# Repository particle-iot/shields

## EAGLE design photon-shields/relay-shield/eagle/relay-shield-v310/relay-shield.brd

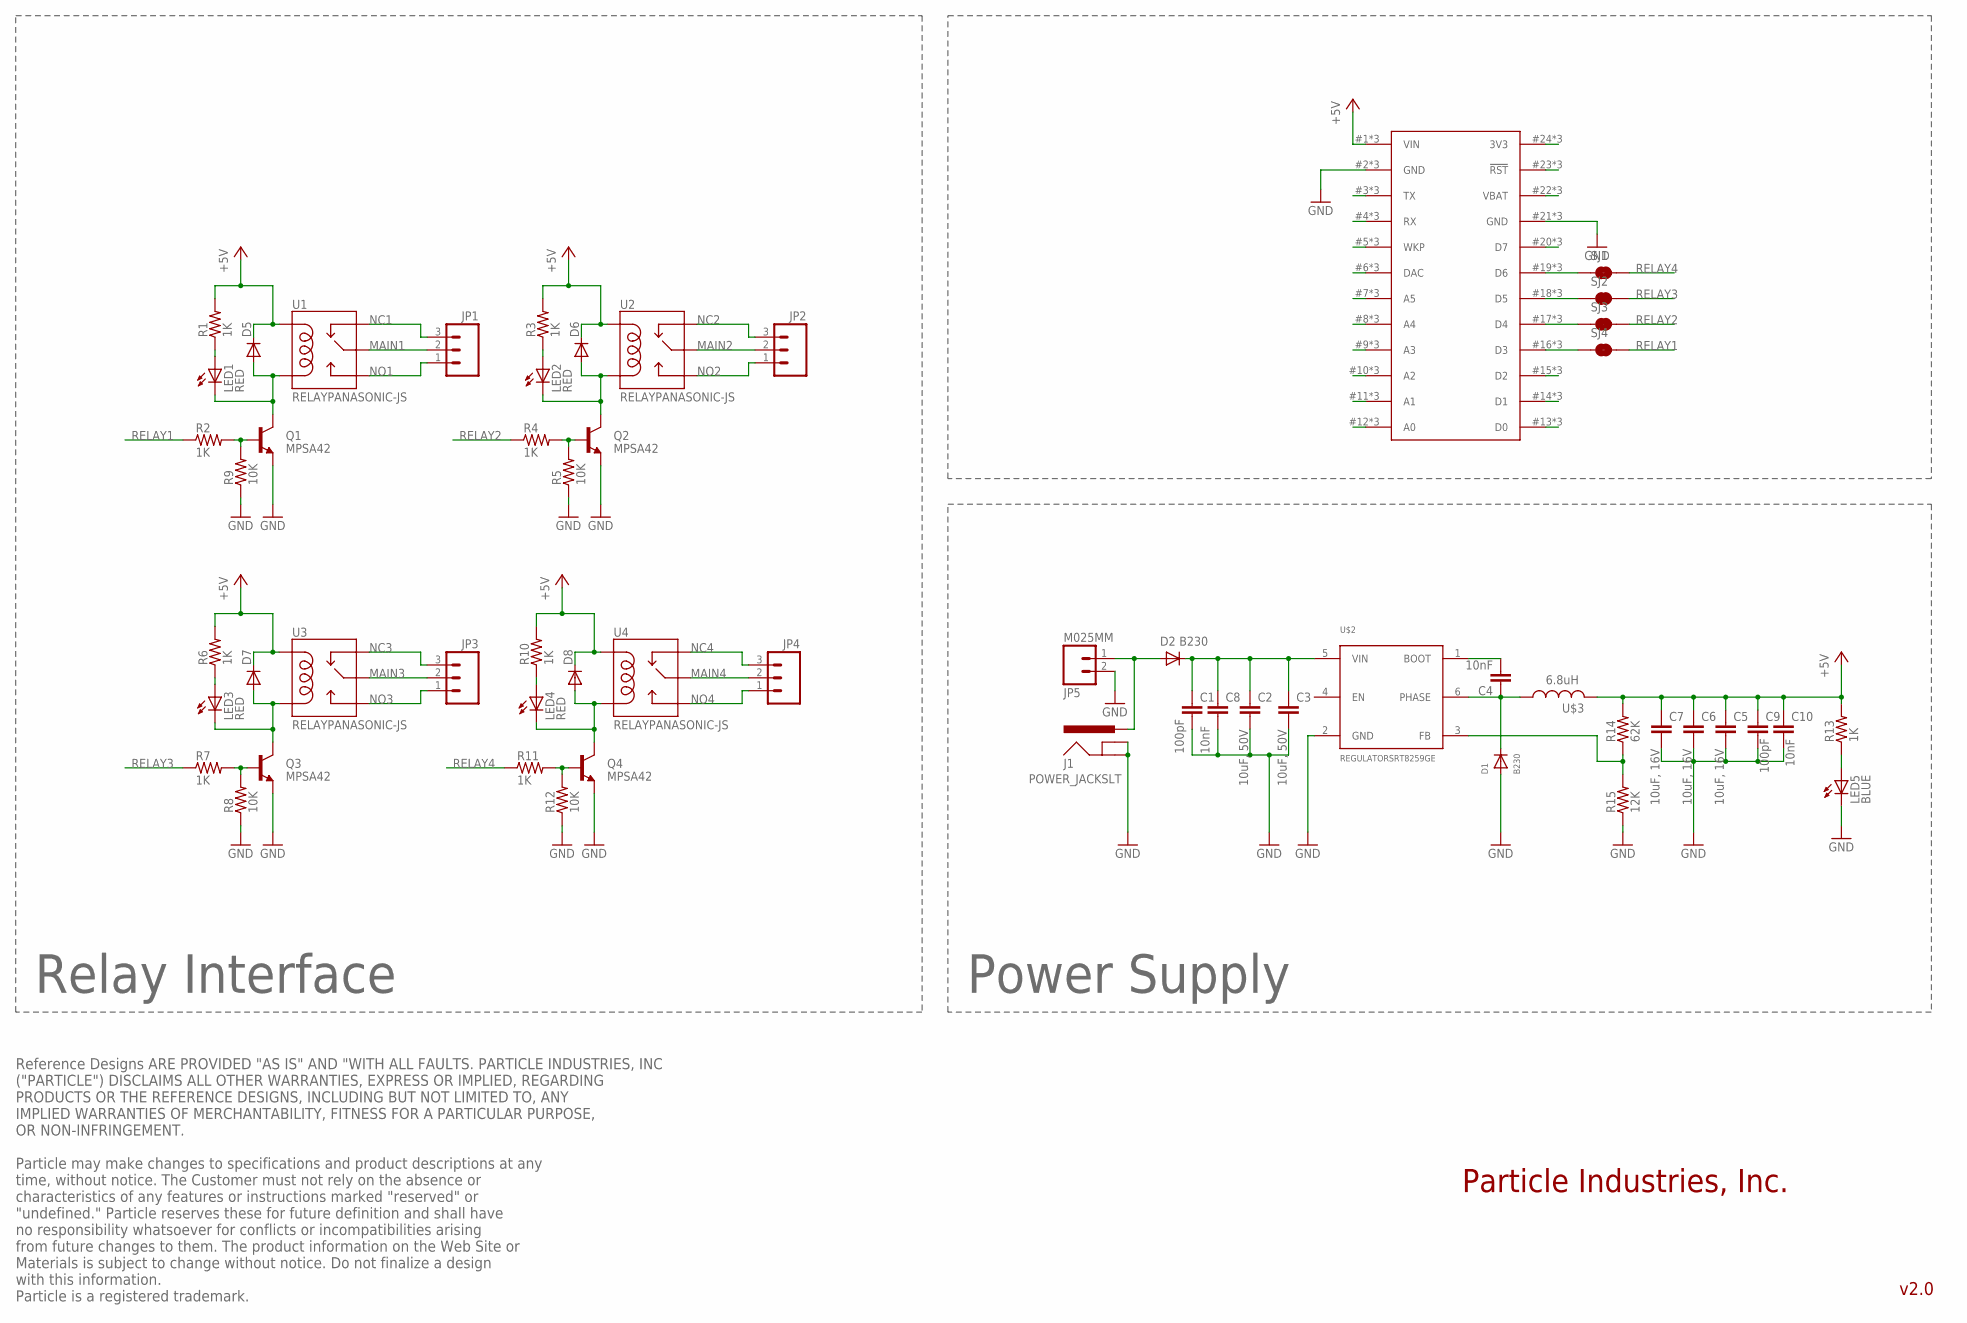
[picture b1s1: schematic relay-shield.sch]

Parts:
C1, C9: 100pF; C0603
C2, C3: 10uF, 50V; 1206
C4: 10nF; 0603-CAP
C5, C6, C7: 10uF, 16V; 1206
C8, C10: 10nF; C0603
D1, D2: B230; SMADIODE
D5, D6, D7, D8: DIODE-SOD123; SOD123
J1: POWER_JACKSLT; POWER_JACK_SLOT
JP1, JP2, JP3, JP4: M03-SCREW-5MM; SCREWTERMINAL-5MM-3
JP5: M025MM; SCREWTERMINAL-5MM-2
LED1, LED2, LED3, LED4: RED; LED-0603
LED5: BLUE; LED-0603
Q1, Q2, Q3, Q4: MPSA42; SOT23
R1, R2, R3, R4, R6, R7, R10, R11, R13: 1K; 0603-RES
R5, R8, R9, R12: 10K; 0603-RES
R14: 62K; 0603-RES
R15: 12K; 0603-RES
SJ1, SJ2, SJ3, SJ4: JUMPER-PAD-2-NC_BY_TRACE; PAD-JUMPER-2-NC_BY_TRACE_YES_SILK
U1, U2, U3, U4: RELAYPANASONIC-JS; JS1-5V-F
U$1: SPARK_CORESTACKABLE; SPARK_CORE_STACKABLE
U$2: REGULATORSRT8259GE; SOT23-6
U$3: INDUCTORS; NR8040T6R8N

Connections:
+5V: C5.1, C6.1, C7.1, C9.1, C10.1, D5.C, D6.C, D7.C, D8.C, R1.2, R3.2, R6.2, R10.2, R13.2, R14.2, U1.COIL1, U2.COIL1, U3.COIL1, U4.COIL1, U$1.1 (VIN), U$1.#1 (VIN), U$1.@1 (VIN), U$3.P$2 (2)
GND: C1.2, C2.2, C3.2, C5.2, C6.2, C7.2, C8.2, C9.2, C10.2, D1.A, J1.GND@1 (GNDBREAK), J1.GND@2 (GND), JP5.2, LED5.C, Q1.2 (E), Q2.2 (E), Q3.2 (E), Q4.2 (E), R5.1, R8.1, R9.1, R12.1, R15.1, U$1.2 (GND), U$1.21 (GND), U$1.#2 (GND), U$1.#21 (GND), U$1.@2 (GND), U$1.@21 (GND), U$2.2 (GND)
MAIN1: JP1.2, U1.COMMON (MAIN)
MAIN2: JP2.2, U2.COMMON (MAIN)
MAIN3: JP3.2, U3.COMMON (MAIN)
MAIN4: JP4.2, U4.COMMON (MAIN)
unnamed: D5.A, LED1.C, Q1.3 (C), U1.COIL2
unnamed: Q2.1 (B), R4.2, R5.2
unnamed: Q1.1 (B), R2.2, R9.2
unnamed: LED1.A, R1.1
unnamed: D6.A, LED2.C, Q2.3 (C), U2.COIL2
unnamed: LED2.A, R3.1
unnamed: Q3.1 (B), R7.2, R8.2
unnamed: D7.A, LED3.C, Q3.3 (C), U3.COIL2
unnamed: LED3.A, R6.1
unnamed: Q4.1 (B), R11.2, R12.2
unnamed: D8.A, LED4.C, Q4.3 (C), U4.COIL2
unnamed: LED4.A, R10.1
unnamed: U$1.15 (D2), U$1.#15 (D2), U$1.@15 (D2)
unnamed: C1.1, C2.1, C3.1, C8.1, D2.C, U$2.5 (VIN)
unnamed: U$1.14 (D1), U$1.#14 (D1), U$1.@14 (D1)
unnamed: LED5.A, R13.1
unnamed: U$1.13 (D0), U$1.#13 (D0), U$1.@13 (D0)
unnamed: U$1.20 (D7), U$1.#20 (D7), U$1.@20 (D7)
unnamed: U$1.22 (VBAT), U$1.#22 (VBAT), U$1.@22 (VBAT)
unnamed: U$1.23 (!RST), U$1.#23 (!RST), U$1.@23 (!RST)
unnamed: U$1.24 (3V3), U$1.#24 (3V3), U$1.@24 (3V3)
unnamed: U$1.12 (A0), U$1.#12 (A0), U$1.@12 (A0)
unnamed: U$1.11 (A1), U$1.#11 (A1), U$1.@11 (A1)
unnamed: U$1.10 (A2), U$1.#10 (A2), U$1.@10 (A2)
unnamed: U$1.9 (A3), U$1.#9 (A3), U$1.@9 (A3)
unnamed: U$1.8 (A4), U$1.#8 (A4), U$1.@8 (A4)
unnamed: U$1.7 (A5), U$1.#7 (A5), U$1.@7 (A5)
unnamed: U$1.6 (DAC), U$1.#6 (DAC), U$1.@6 (DAC)
unnamed: U$1.5 (WKP), U$1.#5 (WKP), U$1.@5 (WKP)
unnamed: U$1.4 (RX), U$1.#4 (RX), U$1.@4 (RX)
unnamed: U$1.3 (TX), U$1.#3 (TX), U$1.@3 (TX)
unnamed: D2.A, J1.PWR, JP5.1
unnamed: SJ1.1, U$1.19 (D6), U$1.#19 (D6), U$1.@19 (D6)
unnamed: C4.1, D1.C, U$2.6 (PHASE), U$3.P$1 (1)
unnamed: C4.2, U$2.1 (BOOT)
unnamed: SJ2.1, U$1.18 (D5), U$1.#18 (D5), U$1.@18 (D5)
unnamed: R14.1, R15.2, U$2.3 (FB)
unnamed: SJ3.1, U$1.17 (D4), U$1.#17 (D4), U$1.@17 (D4)
unnamed: SJ4.1, U$1.16 (D3), U$1.#16 (D3), U$1.@16 (D3)
NC1: JP1.3, U1.CLOSED (NC)
NC2: JP2.3, U2.CLOSED (NC)
NC3: JP3.3, U3.CLOSED (NC)
NC4: JP4.3, U4.CLOSED (NC)
NO1: JP1.1, U1.OPEN (NO)
NO2: JP2.1, U2.OPEN (NO)
NO3: JP3.1, U3.OPEN (NO)
NO4: JP4.1, U4.OPEN (NO)
RELAY1: R2.1, SJ4.2
RELAY2: R4.1, SJ3.2
RELAY3: R7.1, SJ2.2
RELAY4: R11.1, SJ1.2

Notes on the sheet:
Particle Industries, Inc.
Relay Interface
Power Supply
v2.0
6.8uH
Reference Designs ARE PROVIDED "AS IS" AND "WITH ALL FAULTS. PARTICLE INDUSTRIES, INC ("PARTICLE") DISCLAIMS ALL OTHER WARRANTIES, EXPRESS OR IMPLIED, REGARDING PRODUCTS OR THE REFERENCE DESIGNS, INCLUDING BUT NOT LIMITED TO, ANY IMPLIED WARRANTIES OF MERCHANTABILITY, FITNESS FOR A PARTICULAR PURPO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

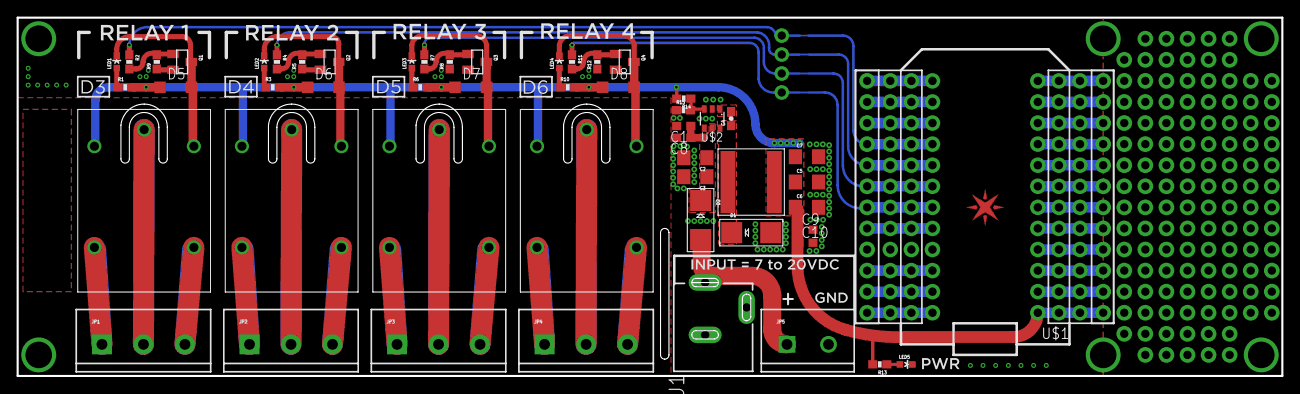
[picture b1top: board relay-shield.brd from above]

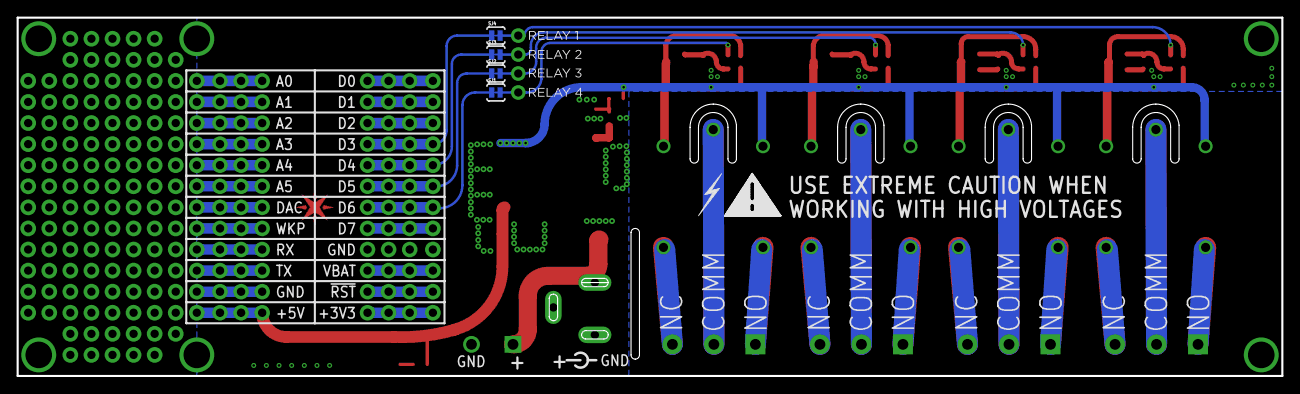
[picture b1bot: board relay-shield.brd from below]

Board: 2 copper layers, 152.4 x 43.2 mm, 58 parts (4 on the bottom side), 57 nets.

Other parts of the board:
E$1: SPARK_LOGO_PLUS_PLANE

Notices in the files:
parts and their libraries:
SparkFun-Connectors: Licensing: CC v3.0 Share-Alike You are welcome to use this library for commercial purposes.
